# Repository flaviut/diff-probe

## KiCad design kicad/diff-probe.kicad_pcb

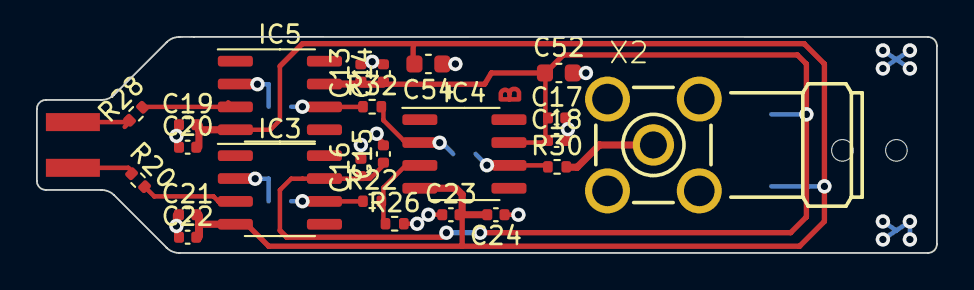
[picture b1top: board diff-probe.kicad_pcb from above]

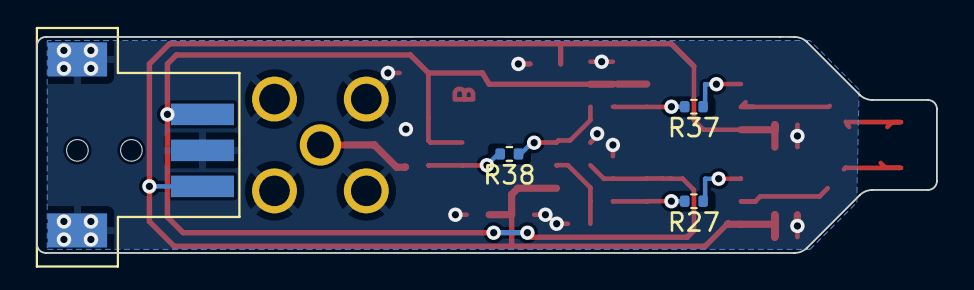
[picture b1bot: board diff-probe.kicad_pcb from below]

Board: 2 copper layers, 50.0 x 12.0 mm, 29 parts (4 on the bottom side), 3 nets.

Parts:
C13, C14, C15, C16, C17, C18, C19, C20, C21, C22, C23, C24: 10nF; C_0402_1005Metric
C52, C54: 1µF; C_0603_1608Metric
IC3, IC4, IC5: LMH6702; SOIC-8_3.9x4.9mm_P1.27mm
J3: HEADER-1X2CARD-EDGE; CARD_EDGE_PADS-1X2
J4: CON-1X3-TAB-AMP-29173-3-NARROW; AMP-29173-3-NARROW
R20, R28: 150Ω; R_0402_1005Metric
R22, R32: 1.1kΩ; R_0402_1005Metric
R26, R27, R37, R38: 220Ω; R_0402_1005Metric
R30: 50Ω; R_0402_1005Metric
X2: SMA--BU-SMA-H; BU-SMA-H

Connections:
GND: C52.2, C54.1, J4.2, J4.P$4, J4.P$5, X2.2, X2.3 (2), X2.4 (2), X2.5 (2)
V+: C52.1, IC3.7 (+VS1), IC4.7 (+VS1), IC5.7 (+VS1), J4.1
V-: C54.2, IC3.4 (-VS1), IC4.4 (-VS1), IC5.4 (-VS1), J4.3
